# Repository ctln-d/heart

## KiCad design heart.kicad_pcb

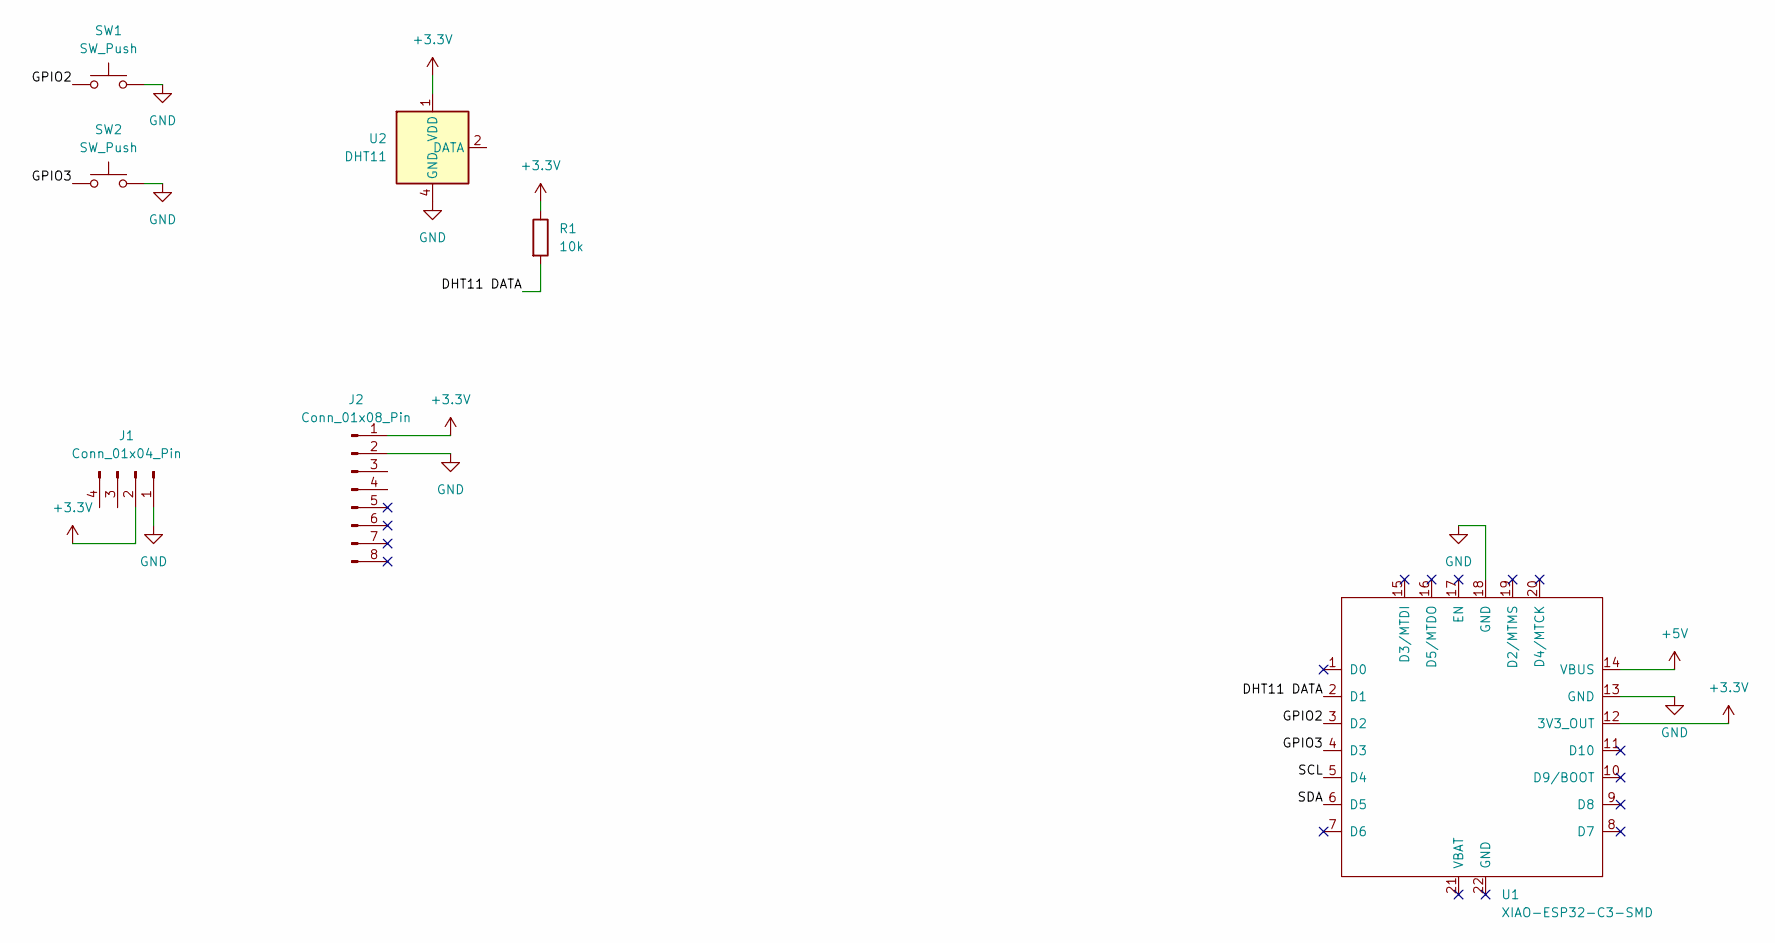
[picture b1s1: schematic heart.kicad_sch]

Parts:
J1: Conn_01x04_Pin; Display_128x64_096_I2C
J2: Conn_01x08_Pin; PinHeader_1x08_P2.54mm_Vertical
R1: 10k; R_Axial_DIN0204_L3.6mm_D1.6mm_P7.62mm_Horizontal
SW1, SW2: SW_Push; SW_Cherry_MX_1.00u_PCB
U1: XIAO-ESP32-C3-SMD
U2: DHT11; Aosong_DHT11_5.5x12.0_P2.54mm

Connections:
+3.3V: J1.2, J2.1, R1.1, U1.12 (3V3_OUT), U2.1 (VDD)
+5V: U1.14 (VBUS)
/DHT11 DATA: R1.2, U1.2 (D1)
/GPIO2: SW1.1, U1.3 (D2)
/GPIO3: SW2.1, U1.4 (D3)
/SCL: U1.5 (D4)
/SDA: U1.6 (D5)
GND: J1.1, J2.2, SW1.2, SW2.2, U1.13 (GND), U1.18 (GND), U2.4 (GND)

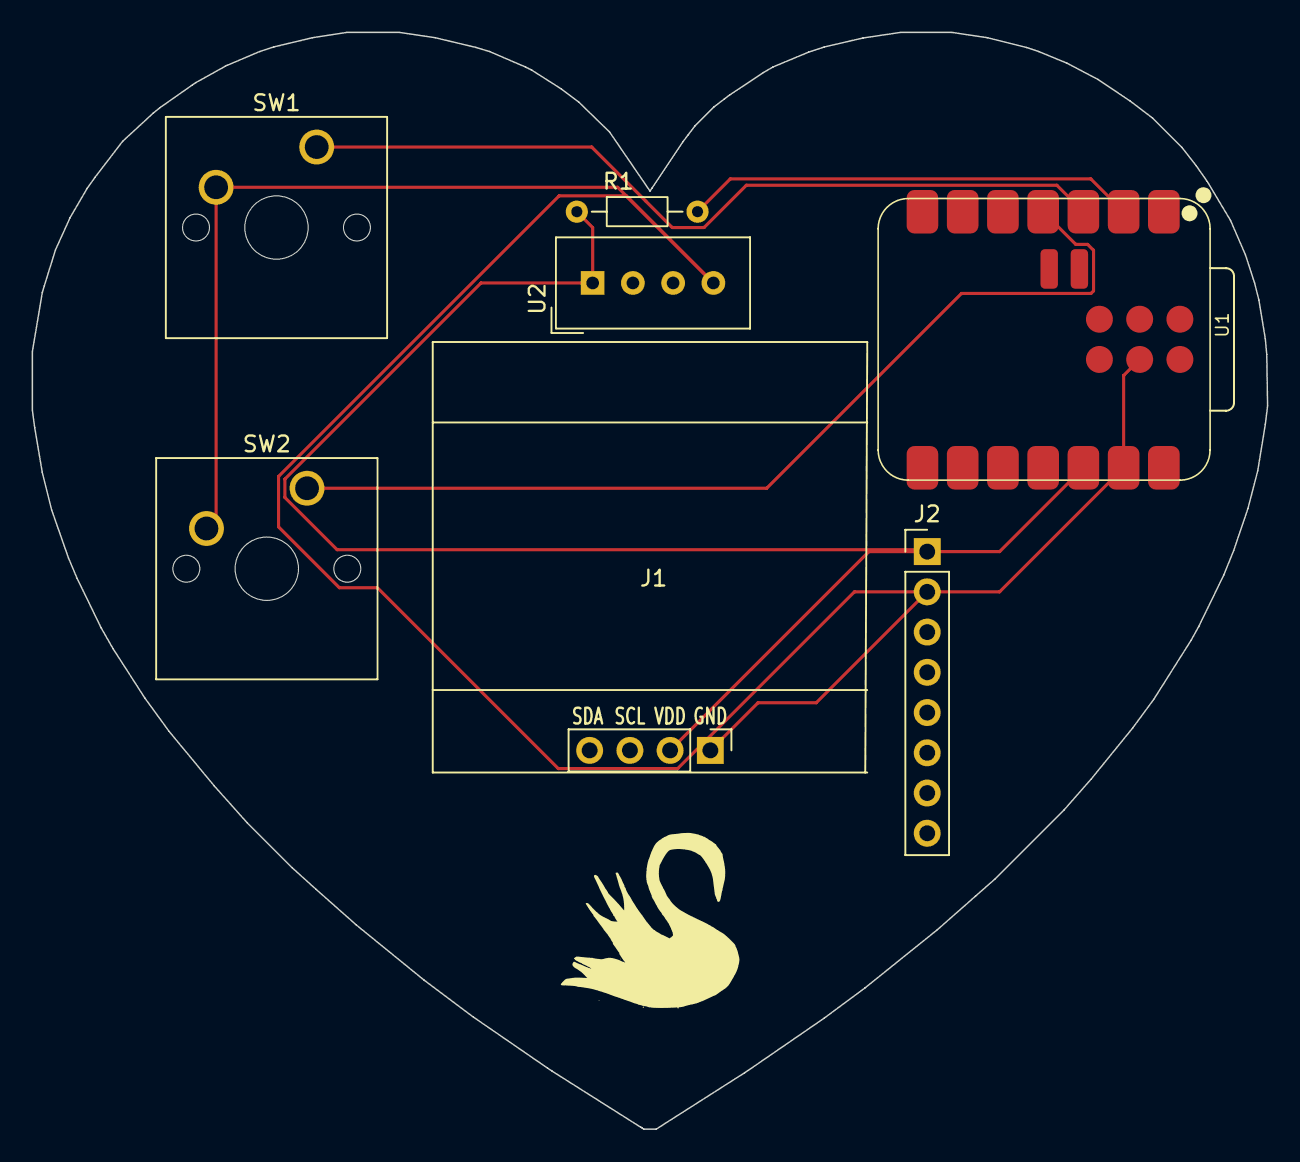
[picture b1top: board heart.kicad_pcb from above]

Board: 2 copper layers, 78.0 x 69.2 mm, 7 parts (0 on the bottom side), 5 nets.
